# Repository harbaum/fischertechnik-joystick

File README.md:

# fischertechnik-joystick

This is a simple joystick interface for fischertechnik. It connects
to any PC and has ft compatible IOs for 8 fire buttons, four digital
direction buttons and four analog axes.

This repository contains the schematic and the board layout in eagle format,
the firmware source code and a 3D printable case design.

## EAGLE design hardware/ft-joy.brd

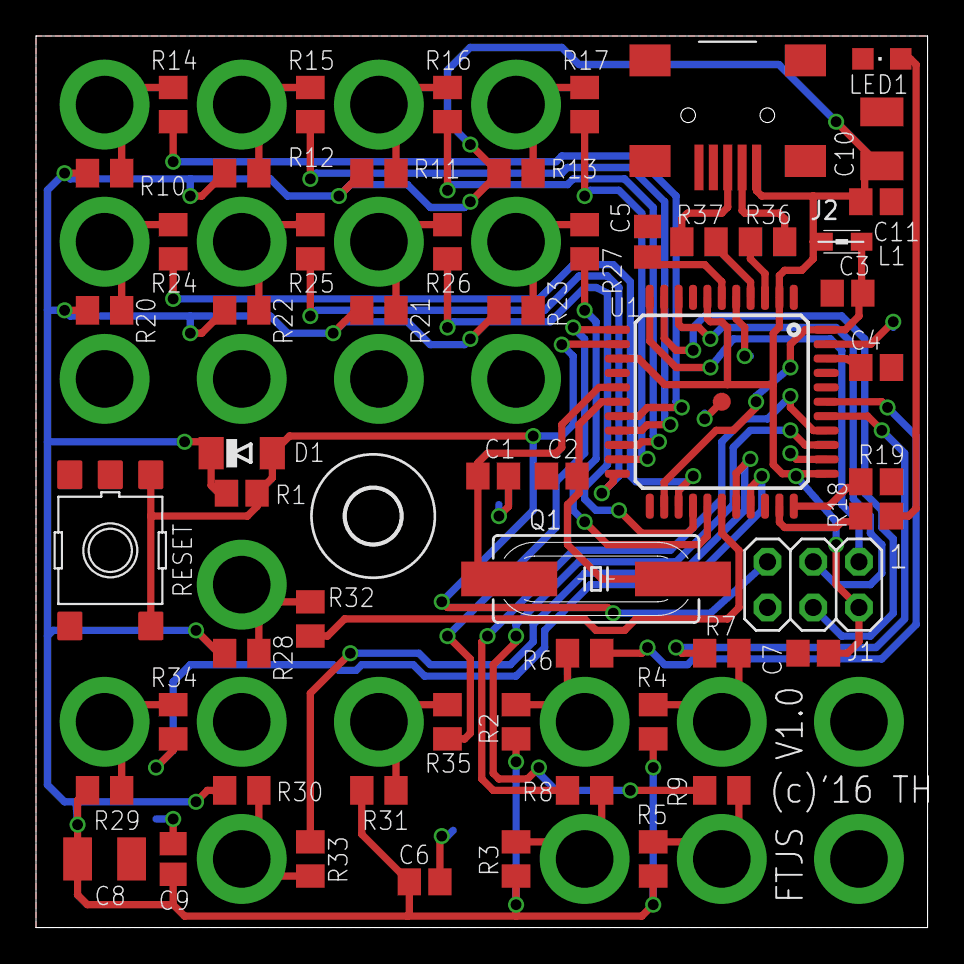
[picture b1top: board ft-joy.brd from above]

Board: 2 copper layers, 49.5 x 49.5 mm, 80 parts (0 on the bottom side), 50 nets.

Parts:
C1, C2: 32pF; C0805
C3, C5: 1µF; C0805
C4, C6, C7, C9, C11: 100nF; C0805
C8, C10: 10µF; SMC_B
D1: CD1206-S01575; MINIMELF
H1: MOUNT-HOLE3.0; 3,0
J1: 3x2M; 2X03
J2: USB-MINI-B%C; USB-MINI-B_2
L1: MH2029-300Y; 0805
LED1: green; CHIPLED_0805
P1: Lx; FT-HUELSE
P2: Ly; FT-HUELSE
P3: LG; FT-HUELSE
P4: Rx; FT-HUELSE
P5: Ry; FT-HUELSE
P6: RG; FT-HUELSE
P7: B0; FT-HUELSE
P8: B1; FT-HUELSE
P9: BG0; FT-HUELSE
P10: B2; FT-HUELSE
P11, P13: B3; FT-HUELSE
P12: BG1; FT-HUELSE
P14: B4; FT-HUELSE
P15: BG2; FT-HUELSE
P16: B5; FT-HUELSE
P17: B6; FT-HUELSE
P18: BG3; FT-HUELSE
P19: DU; FT-HUELSE
P20: DD; FT-HUELSE
P21: DL; FT-HUELSE
P22: DR; FT-HUELSE
P23: DG; FT-HUELSE
Q1: 16MHz; HC49UP
R1, R19: 10K; R0805
R2, R3, R4, R5: 5k1; M0805
R6, R7, R8, R9, R14, R15, R16, R17, R24, R25, R26, R27, R32, R33, R34, R35: 47k; M0805
R10, R11, R12, R13, R20, R21, R22, R23, R28, R29, R30, R31: 4k7; M0805
R18: 220; R0805
R36, R37: 22; M0805
RESET: TS42
U1: ATMEGA32U4-XUAU; TQFP44-PAD

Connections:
+5V: C6.1, C7.1, C8.+, C9.1, C10.+, C11.1, D1.C, J1.2, J2.5, L1.1, R1.1, R2.1, R3.1, R4.1, R5.1, R10.1, R11.1, R12.1, R13.1, R20.1, R21.1, R22.1, R23.1, R28.1, R29.1, R30.1, R31.1, U1.2, U1.7, U1.14, U1.34
ADC4: R6.1, U1.39
ADC5: R7.1, U1.38
ADC6: R8.1, U1.37
ADC7: R9.1, U1.36
AREF: C4.1, U1.42
AVCC: C3.1, L1.2, U1.24, U1.44
D+: J2.3, R37.1
D-: J2.4, R36.1
GND: C1.1, C2.1, C3.2, C4.2, C5.2, C6.2, C7.2, C8.-, C9.2, C10.-, C11.2, J1.6, J2.1, J2.6, J2.7, J2.8, J2.9, LED1.C, P3.D1, P6.D1, P9.D1, P12.D1, P15.D1, P18.D1, P23.D1, R19.2, RESET.3, RESET.4, RESET.5, U1.5, U1.15, U1.23, U1.35, U1.43, U1.P$1
HWB: R19.1, U1.33
LED: R18.1, U1.32
MISO: J1.1, U1.11
MOSI: J1.4, U1.10
unnamed: P2.D1, R4.2, R7.2
unnamed: P4.D1, R3.2, R8.2
unnamed: P5.D1, R5.2, R9.2
unnamed: P7.D1, R10.2, R14.2
unnamed: P8.D1, R12.2, R15.2
unnamed: P10.D1, R11.2, R16.2
unnamed: LED1.A, R18.2
unnamed: P11.D1, R13.2, R17.2
unnamed: P13.D1, R20.2, R24.2
unnamed: P14.D1, R22.2, R25.2
unnamed: P16.D1, R21.2, R26.2
unnamed: P17.D1, R23.2, R27.2
unnamed: P19.D1, R28.2, R32.2
unnamed: P20.D1, R30.2, R33.2
unnamed: P21.D1, R29.2, R34.2
unnamed: P22.D1, R31.2, R35.2
unnamed: P1.D1, R2.2, R6.2
PB4: R32.1, U1.28
PB5: R33.1, U1.29
PB6: R34.1, U1.30
PB7: R35.1, U1.12
PD0: R14.1, U1.18
PD1: R15.1, U1.19
PD2: R16.1, U1.20
PD3: R17.1, U1.21
PD4: R24.1, U1.25
PD5: R25.1, U1.22
PD6: R26.1, U1.26
PD7: R27.1, U1.27
RD+: R37.2, U1.4
RD-: R36.2, U1.3
RESET: D1.A, J1.5, R1.2, RESET.1, RESET.2, U1.13
SCK: J1.3, U1.9
UCAP: C5.1, U1.6
XTAL1: C2.2, Q1.2, U1.17
XTAL2: C1.2, Q1.1, U1.16

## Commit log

2017-10-02 Initial release
2017-10-02 Some images
2017-10-02 Rescale image
2017-10-02 Adjusted USB vid/pid
2017-10-02 More fotos
